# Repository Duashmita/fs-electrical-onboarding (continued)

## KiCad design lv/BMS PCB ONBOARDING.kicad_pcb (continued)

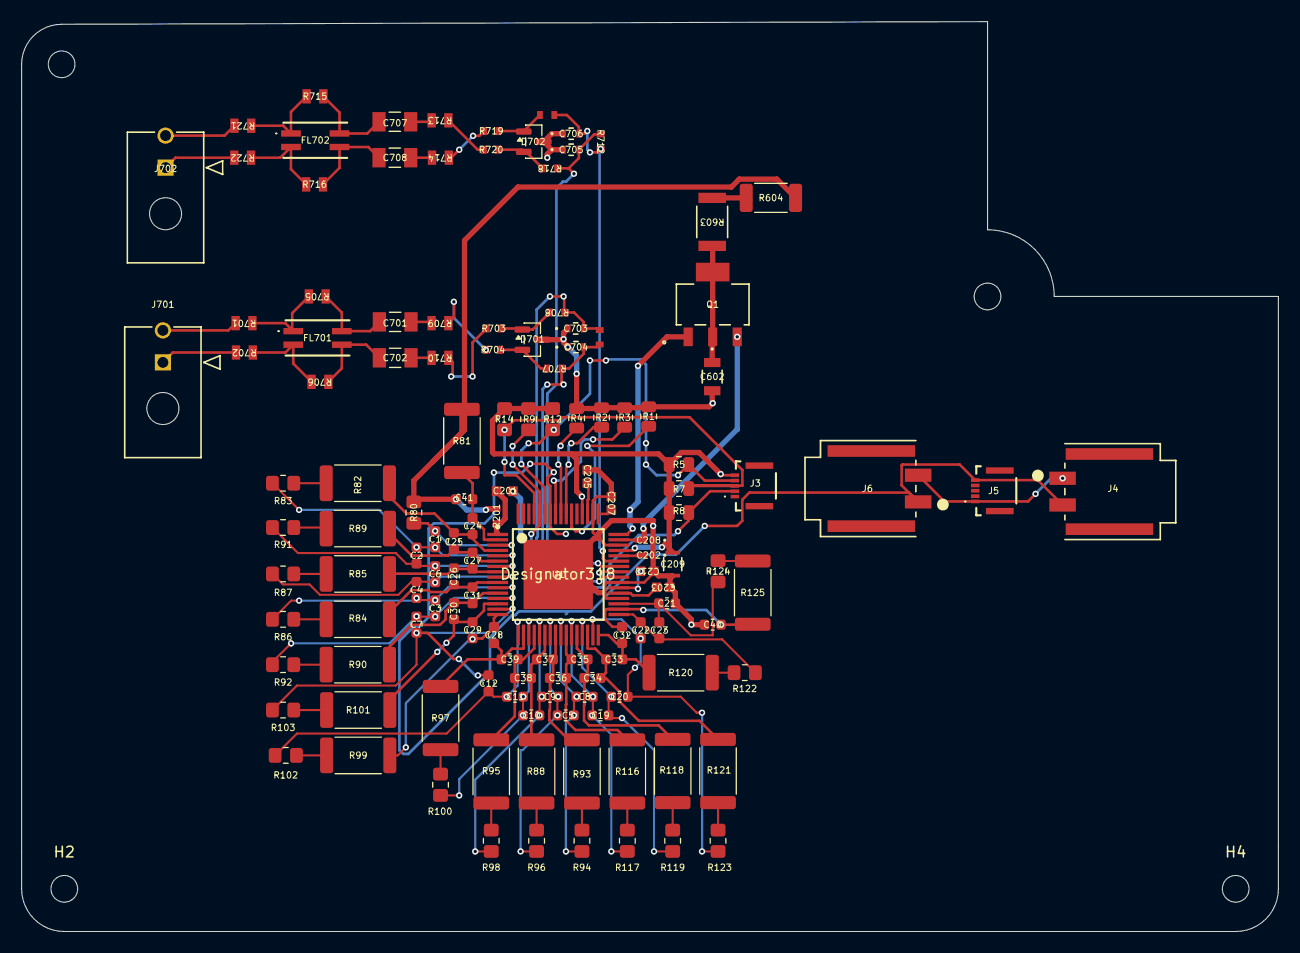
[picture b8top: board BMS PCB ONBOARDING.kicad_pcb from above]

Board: 4 copper layers, 117.8 x 85.2 mm, 137 parts (0 on the bottom side), 100 nets.
